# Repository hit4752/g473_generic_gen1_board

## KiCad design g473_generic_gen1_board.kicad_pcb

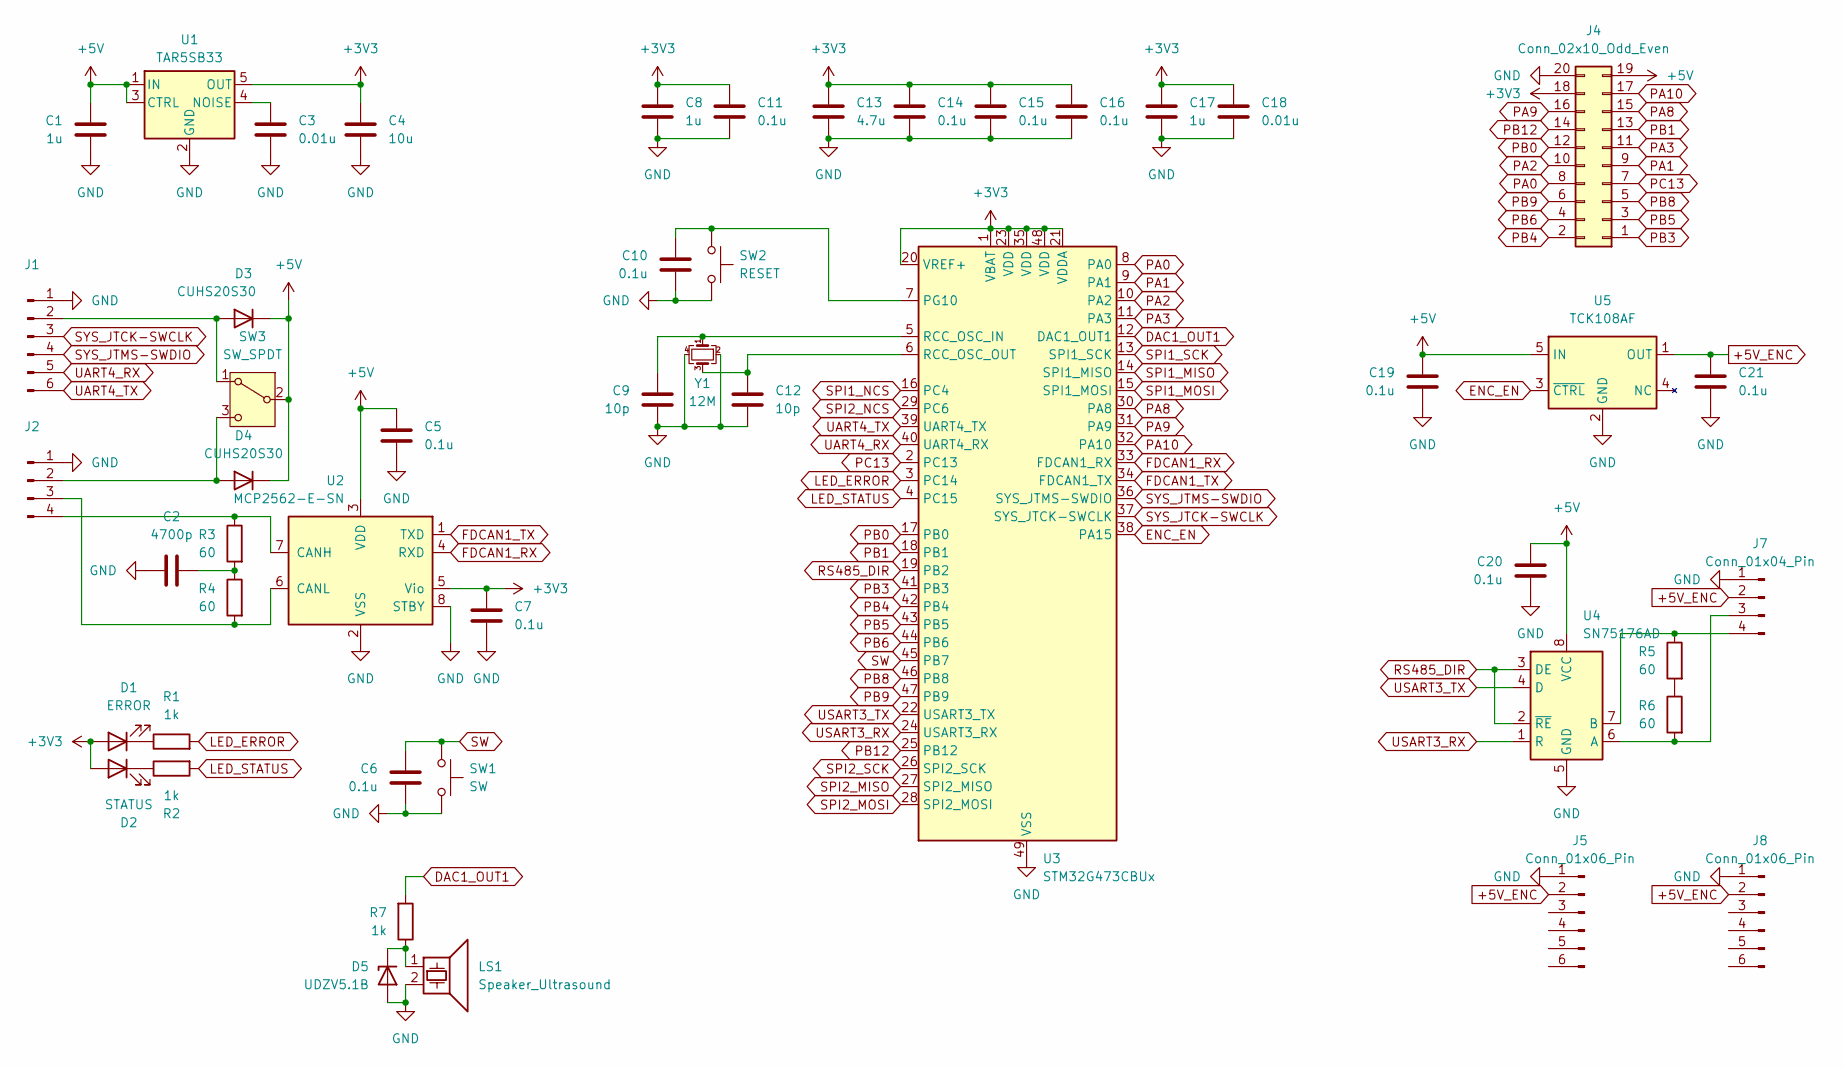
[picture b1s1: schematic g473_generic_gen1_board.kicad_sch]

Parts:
C1, C8, C17: 1u; C_0603_1608Metric
C2: 4700p; C_0603_1608Metric
C3, C18: 0.01u; C_0603_1608Metric
C4: 10u; C_0603_1608Metric
C5, C6, C7, C10, C11, C14, C15, C16, C19, C20, C21: 0.1u; C_0603_1608Metric
C9, C12: 10p; C_0603_1608Metric
C13: 4.7u; C_0603_1608Metric
D1: ERROR; LED_0603_1608Metric
D2: STATUS; LED_0603_1608Metric
D3, D4: CUHS20S30; D_TUMD2
D5: UDZV5.1B; D_SOD-323
J1, J5, J8: Conn_01x06_Pin; Neltron_3750R-06_1x06_P2.54mm_Horizontal
J2, J7: Conn_01x04_Pin; Neltron_3750R-04_1x04_P2.54mm_Horizontal
J4: Conn_02x10_Odd_Even; PinSocket_2x10_P2.54mm_Vertical
LS1: Speaker_Ultrasound; Buzzer_Murata_PKLCS1212E
R1, R2, R7: 1k; R_0603_1608Metric
R3, R4, R5, R6: 60; R_0603_1608Metric
SW1: SW; SW_PUSH_6mm
SW2: RESET; SW_PUSH_6mm
SW3: SW_SPDT; SW_Slide_SPDT_Angled_SK-12D11VG3
U1: TAR5SB33; SOT-23-5
U2: MCP2562-E-SN; SOIC-8_3.9x4.9mm_P1.27mm
U3: STM32G473CBUx; QFN-48-1EP_7x7mm_P0.5mm_EP5.6x5.6mm
U4: SN75176AD; SOIC-8_3.9x4.9mm_P1.27mm
U5: TCK108AF; SOT-23-5
Y1: 12M; Crystal_SMD_3225-4Pin_3.2x2.5mm

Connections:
+3V3: C4.1, C7.1, C8.1, C11.1, C13.1, C14.1, C15.1, C16.1, C17.1, C18.1, D1.2 (A), D2.2 (A), J4.18, U1.5 (OUT), U2.5 (Vio), U3.1 (VBAT), U3.20 (VREF+), U3.21 (VDDA), U3.23 (VDD), U3.35 (VDD), U3.48 (VDD)
+5V: C1.1, C5.1, C19.1, C20.1, D3.1 (K), D4.1 (K), J4.19, SW3.2 (B), U1.1 (IN), U1.3 (CTRL), U2.3 (VDD), U4.8 (VCC), U5.5 (IN)
+5V_ENC: C21.1, J5.2, J7.2, J8.2, U5.1 (OUT)
DAC1_OUT1: R7.2, U3.12 (DAC1_OUT1)
ENC_EN: U3.38 (PA15), U5.3 (~CTRL)
FDCAN1_RX: U2.4 (RXD), U3.33 (FDCAN1_RX)
FDCAN1_TX: U2.1 (TXD), U3.34 (FDCAN1_TX)
GND: C1.2, C2.2, C3.2, C4.2, C5.2, C6.2, C7.2, C8.2, C9.2, C10.2, C11.2, C12.2, C13.2, C14.2, C15.2, C16.2, C17.2, C18.2, C19.2, C20.2, C21.2, D5.2 (A), J1.1, J2.1, J4.20, J5.1, J7.1, J8.1, LS1.2, SW1.2, SW2.2, U1.2 (GND), U2.2 (VSS), U2.8 (STBY), U3.49 (VSS), U4.5 (GND), U5.2 (GND), Y1.2, Y1.4
LED_ERROR: R1.2, U3.3 (PC14)
LED_STATUS: R2.2, U3.4 (PC15)
unnamed: C2.1, R3.2, R4.1
unnamed: D1.1 (K), R1.1
unnamed: D2.1 (K), R2.1
unnamed: D3.2 (A), J1.2, SW3.1 (A)
unnamed: D4.2 (A), J2.2, SW3.3 (C)
unnamed: D5.1 (K), LS1.1, R7.1
unnamed: J2.3, R4.2, U2.6 (CANL)
unnamed: J2.4, R3.1, U2.7 (CANH)
unnamed: J7.3, R6.2, U4.6 (A)
unnamed: J7.4, R5.1, U4.7 (B)
unnamed: R5.2, R6.1
unnamed: C3.1, U1.4 (NOISE)
unnamed: C9.1, U3.5 (RCC_OSC_IN), Y1.1
unnamed: C12.1, U3.6 (RCC_OSC_OUT), Y1.3
unnamed: C10.1, SW2.1, U3.7 (PG10)
PA0: J4.8, U3.8 (PA0)
PA1: J4.9, U3.9 (PA1)
PA2: J4.10, U3.10 (PA2)
PA3: J4.11, U3.11 (PA3)
PA8: J4.15, U3.30 (PA8)
PA9: J4.16, U3.31 (PA9)
PA10: J4.17, U3.32 (PA10)
PB0: J4.12, U3.17 (PB0)
PB1: J4.13, U3.18 (PB1)
PB3: J4.1, U3.41 (PB3)
PB4: J4.2, U3.42 (PB4)
PB5: J4.3, U3.43 (PB5)
PB6: J4.4, U3.44 (PB6)
PB8: J4.5, U3.46 (PB8)
PB9: J4.6, U3.47 (PB9)
PB12: J4.14, U3.25 (PB12)
PC13: J4.7, U3.2 (PC13)
RS485_DIR: U3.19 (PB2), U4.2 (~RE), U4.3 (DE)
SPI1_MISO: U3.14 (SPI1_MISO)
SPI1_MOSI: U3.15 (SPI1_MOSI)
SPI1_NCS: U3.16 (PC4)
SPI1_SCK: U3.13 (SPI1_SCK)
SPI2_MISO: U3.27 (SPI2_MISO)
SPI2_MOSI: U3.28 (SPI2_MOSI)
SPI2_NCS: U3.29 (PC6)
SPI2_SCK: U3.26 (SPI2_SCK)
SW: C6.1, SW1.1, U3.45 (PB7)
SYS_JTCK-SWCLK: J1.3, U3.37 (SYS_JTCK-SWCLK)
SYS_JTMS-SWDIO: J1.4, U3.36 (SYS_JTMS-SWDIO)
UART4_RX: J1.5, U3.40 (UART4_RX)
UART4_TX: J1.6, U3.39 (UART4_TX)
USART3_RX: U3.24 (USART3_RX), U4.1 (R)
USART3_TX: U3.22 (USART3_TX), U4.4 (D)

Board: 4 copper layers, 49 parts (23 on the bottom side), 50 nets, no tracks yet.
